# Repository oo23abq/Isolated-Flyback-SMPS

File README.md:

# Isolated-Flyback-SMPS-Project-
A breakdown of my first independent PCB project, which was the design of a DC-DC  switch-mode power supply (SMPS) in the flyback converter topology.

## Repository Structure

```markdown

```text
├── docs/                                       # General Documentation 
│   └── report.md                               # Lab Test Report
├── gerbers/                                    # Manufacturing Files
│   └── flybackgerbers.zip                      # Gerber and Drill Archives
├── images/                                     # 3D Renders 
│   ├── lt8300flyback_bottom.png                # Bottom Layer 
│   └── lt8300flyback_top.png                   # Top Layer
├── kicad/                                      # KiCAD Project Files 
│   ├── LT8300_Flyback_RevA.kicad_pcb           # PCB Board File
│   ├── LT8300_Flyback_RevA.kicad_sch           # Schematic File
│   └── LT8300flyback_bom.csv                   # Bill of Materials
├── ltspice/                                    # Analogue Simulation 
│   └── waveform.png                            # LTspice Transient Simulation 
├── testing/                                    # Lab Testing
│   ├── oscilloscopeinput.png                   # Input Voltage (P-Coil)
│   ├── oscilloscopeoutput.png                  # Output Voltage (S-Coil)
│   └── testsetup.png                           # Bench Test Setup 
├── LICENSE                                     # License file
└── README.md                                   # Project documentation and summary

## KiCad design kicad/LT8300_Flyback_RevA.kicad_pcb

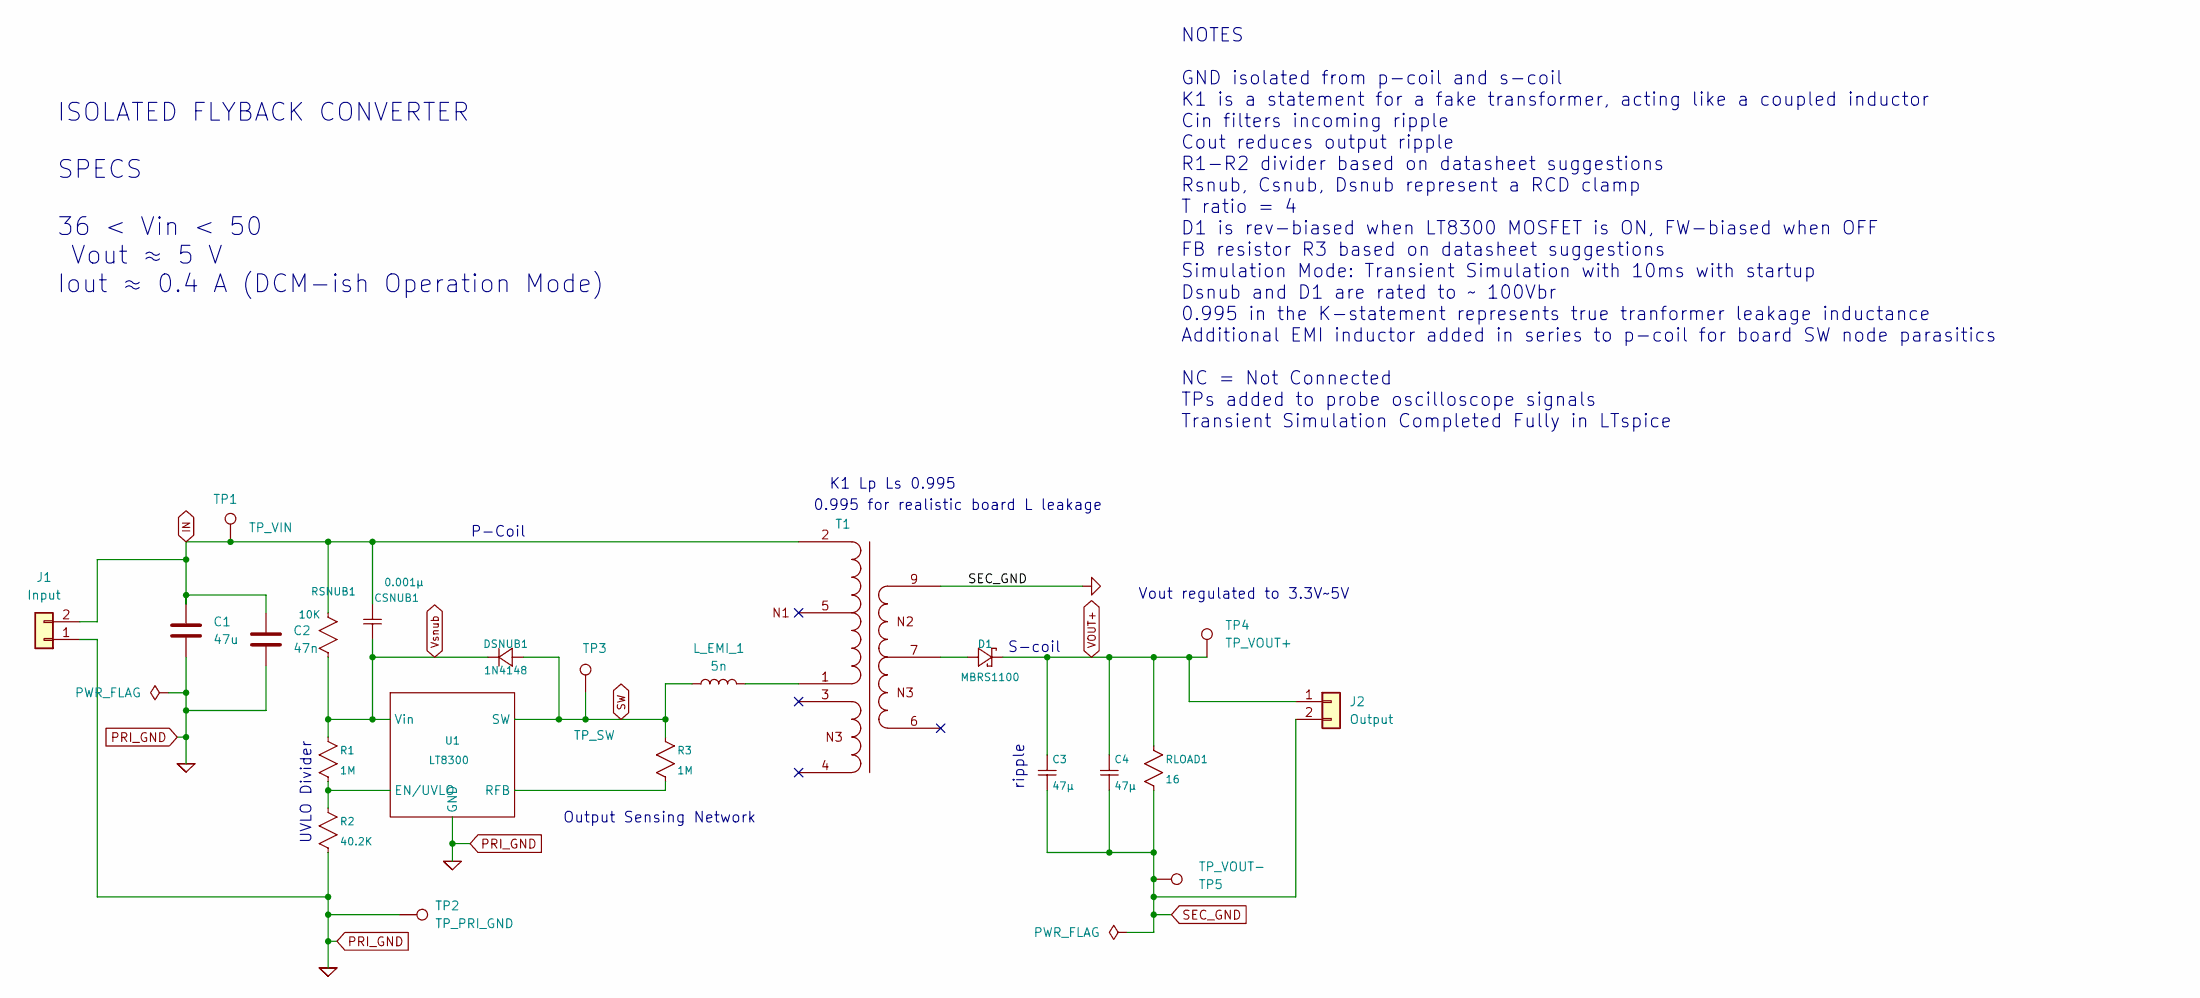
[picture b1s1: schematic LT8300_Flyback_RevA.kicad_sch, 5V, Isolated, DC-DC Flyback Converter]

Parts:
C1: 47u; C_1210_3225Metric
C2: 47n; C_0805_2012Metric
C3, C4: 47µ; C_1210_3225Metric
CSNUB1: 0.001µ; C_0805_2012Metric
D1: MBRS1100; D_SMB
DSNUB1: 1N4148; D_SOD-123
J1: Input; TerminalBlock_Phoenix_MKDS-1,5-2-5.08_1x02_P5.08mm_Horizont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
J2: Output; TerminalBlock_Phoenix_MKDS-1,5-2-5.08_1x02_P5.08mm_Horizont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
L_EMI_1: 5n; L_0805_2012Metric
R1, R3: 1M; R_0805_2012Metric
R2: 40.2K; R_0805_2012Metric
RLOAD1: 16; R_2512_6332Metric
RSNUB1: 10K; R_1206_3216Metric
T1: EPQ13_6389_10PINS_750318525; T_Wurth_WE-FLYTI-EPQ13_6389_10PINS; Part Number 750318525
TP1: TP_VIN; TestPoint_Pad_1.5x1.5mm
TP2: TP_PRI_GND; TestPoint_Pad_1.5x1.5mm
TP3: TP_SW; TestPoint_Pad_1.5x1.5mm
TP4: TP_VOUT+; TestPoint_Pad_1.5x1.5mm
TP5: TP_VOUT-; TestPoint_Pad_1.5x1.5mm
U1: LT8300; MSOP-8-1EP_3x3mm_P0.65mm_EP1.5x1.8mm

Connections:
IN: C1.1, C2.1, CSNUB1.2, J1.2, RSNUB1.2, T1.2, TP1.1
unnamed: D1.2 (+), T1.7, T1.8
unnamed: L_EMI_1.2, T1.1
unnamed: R1.2, R2.1, U1.1 (EN/UVLO)
unnamed: R3.2, U1.3 (RFB)
PRI_GND: C1.2, C2.2, J1.1, R2.2, TP2.1, U1.2 (GND)
SEC_GND: C3.2, C4.2, J2.2, RLOAD1.2, T1.9, T1.10, TP5.1
SW: DSNUB1.1 (+), L_EMI_1.1, R3.1, TP3.1, U1.4 (SW)
VOUT+: C3.1, C4.1, D1.1 (-), J2.1, RLOAD1.1, TP4.1
Vsnub: CSNUB1.1, DSNUB1.2 (-), R1.1, RSNUB1.1, U1.5 (Vin)

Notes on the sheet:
S-coil
K1 Lp Ls 0.995
UVLO Divider
NOTES GND isolated from p-coil and s-coil K1 is a statement for a fake transformer, acting like a coupled inductor Cin filters incoming ripple Cout reduces output ripple R1-R2 divider based on datasheet suggestions Rsnub, Csnub, Dsnub represent a RCD clamp T ratio = 4 D1 is rev-biased when LT8300 M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
P-Coil
ripple
Vout regulated to 3.3V~5V
ISOLATED FLYBACK CONVERTER SPECS 36 < Vin < 50 Vout ≈ 5 V Iout ≈ 0.4 A (DCM-ish Operation Mode)
0.995 for realistic board L leakage
Output Sensing Network

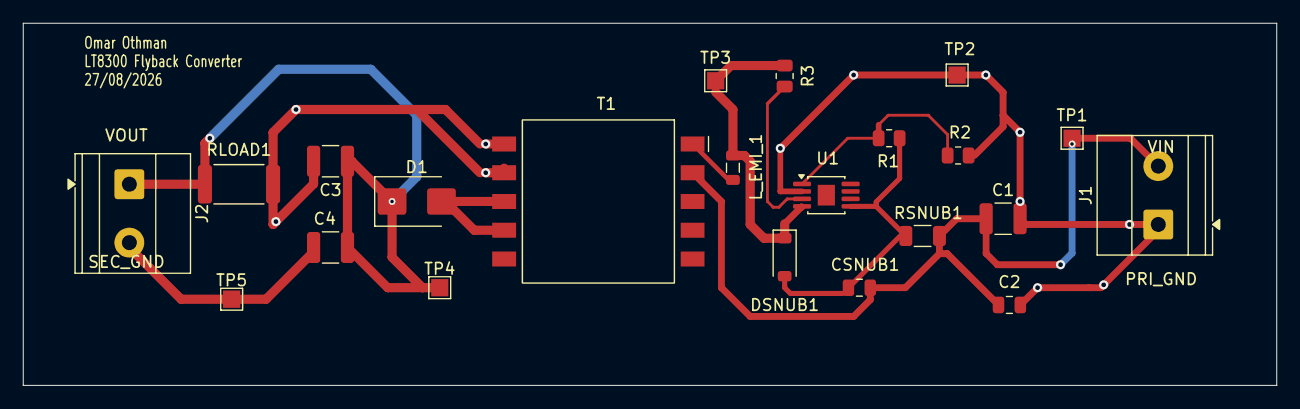
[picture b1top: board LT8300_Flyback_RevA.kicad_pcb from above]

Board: 2 copper layers, 109.0 x 31.5 mm, 22 parts (0 on the bottom side), 10 nets.
